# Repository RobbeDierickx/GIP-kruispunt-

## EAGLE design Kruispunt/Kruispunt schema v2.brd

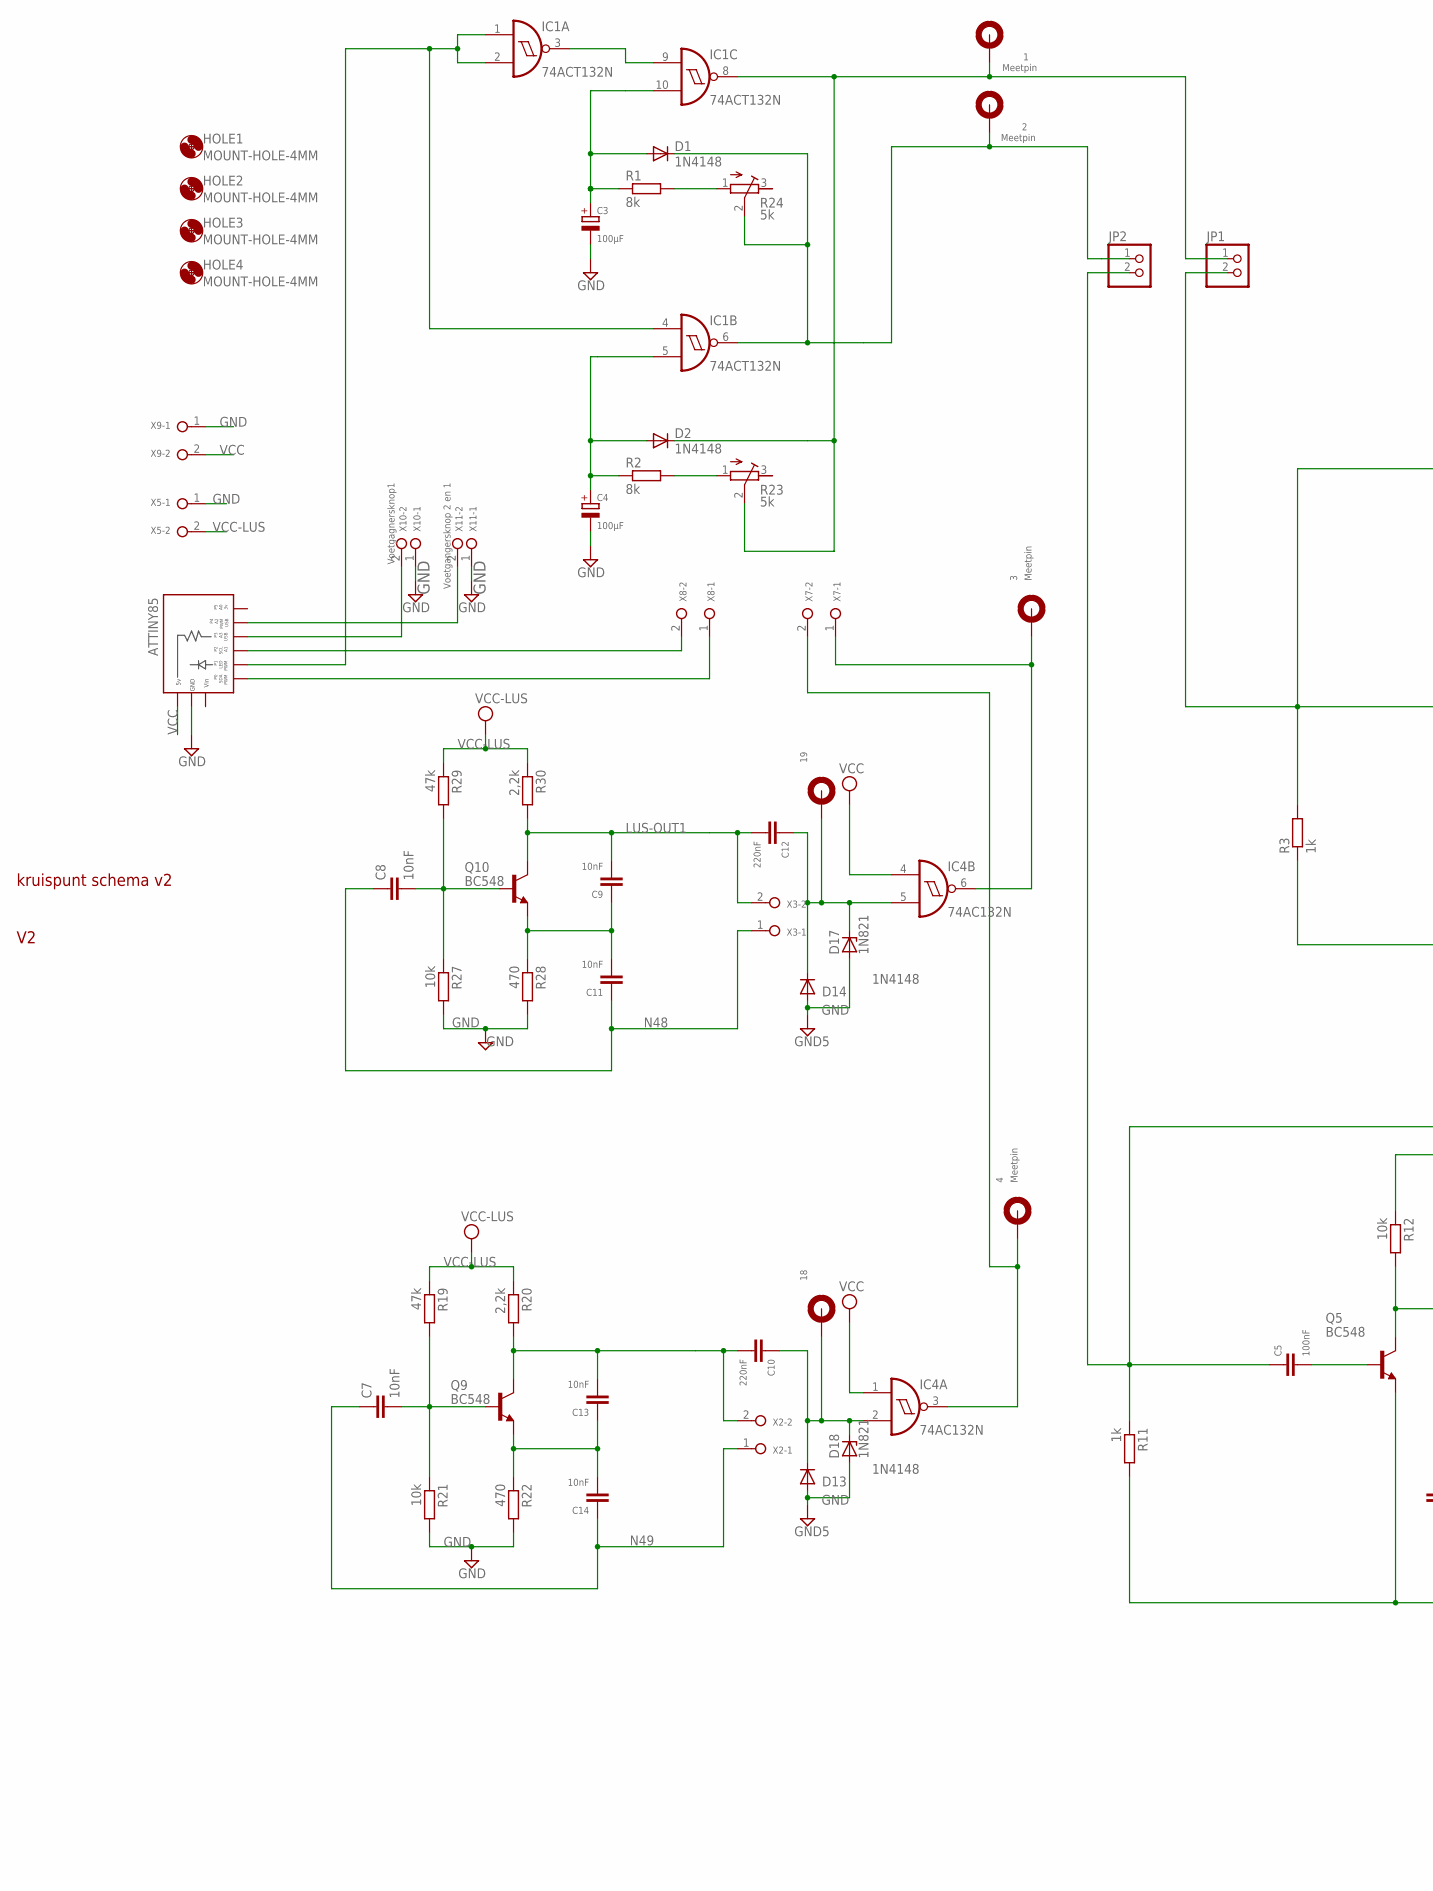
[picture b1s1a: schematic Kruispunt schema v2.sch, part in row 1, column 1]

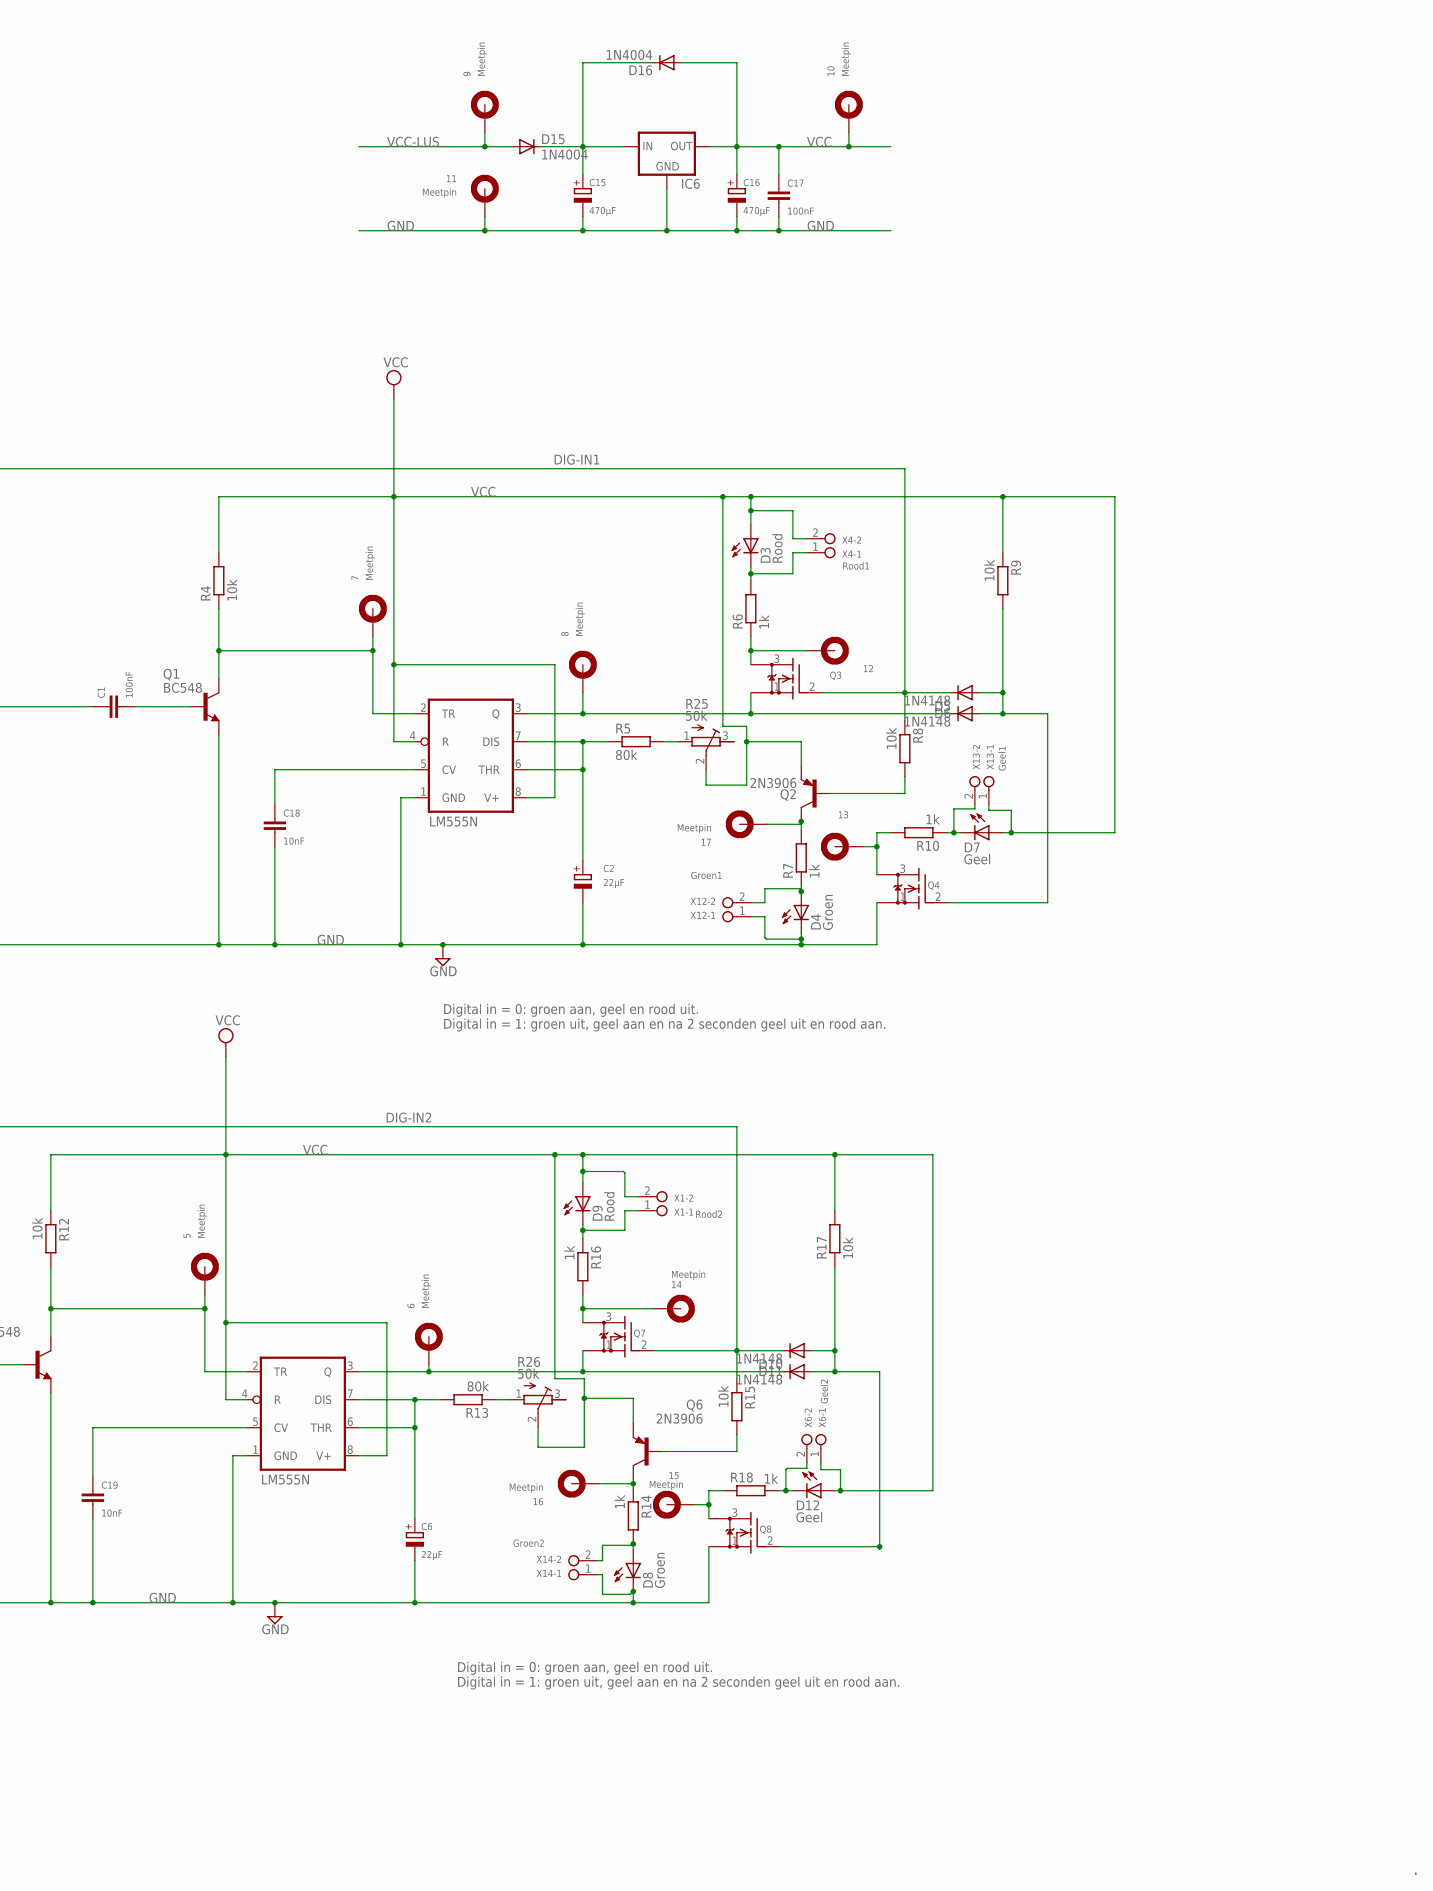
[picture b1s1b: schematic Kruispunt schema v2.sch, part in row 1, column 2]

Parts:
1, 2, 3, 4, 5, 6, 7, 8, 9, 10, 11, 14, 15, 16, 17: Meetpin; PAD
12, 13, 18, 19: WIREPAD; PAD
ATTINY85: DIGISPARK
C1, C5, C17: 100nF; CERAMIC-CAP-C050-025X075
C2, C6: 22µF; ELCO-2.5MMLEAD
C3, C4: 100µF; ELCO-2.5MMLEAD
C7, C8, C9, C11, C13, C14, C18, C19: 10nF; CERAMIC-CAP-C050-025X075
C10, C12: 220nF; CERAMIC-CAP-C025_050-035X075
C15, C16: 470µF; ELCO-5,0MMLEAD
D1, D2, D5, D6, D10, D11, D13, D14: 1N4148; DO35-7
D3, D9: Rood; LED3MM
D4, D8: Groen; LED3MM
D7, D12: Geel; LED3MM
D15, D16: 1N4004; DO35-7
D17, D18: 1N821; DO35Z10
HOLE1, HOLE2, HOLE3, HOLE4: MOUNT-HOLE-4MM; 4,0
IC1: 74ACT132N; DIL14
IC2, IC3: LM555N; DIL08
IC4: 74AC132N; DIL14
IC6: LM78XX-TO220LM78XX-HEATSINK; LM78XX-HEATSINK
JP1, JP2: PINHD-1X2; 1X02
Q1, Q5, Q9, Q10: BC548; TO92-CBE
Q2, Q6: 2N3906; TO92-EBC
Q3, Q4, Q7, Q8: 2N7000; TO-92
R1, R2: 8k; 0207/10
R3, R6, R7, R10, R11, R14, R16, R18: 1k; 0207/10
R4, R8, R9, R12, R15, R17, R21, R27: 10k; 0207/10
R5, R13: 80k; 0207/10
R19, R29: 47k; 0207/10
R20, R30: 2,2k; 0207/10
R22, R28: 470; 0207/10
R23, R24: 5k; RTRIM64W
R25, R26: 50k; RTRIM64W
X1: Rood2; W237-132
X2, X3, X5, X7, X8, X9: TERMINAL-5MM-2POLE; W237-132
X4: Rood1; W237-132
X6: Geel2; W237-132
X10: Voetgagnersknop1; W237-132
X11: Voetgangersknop 2 en 1; W237-132
X12: Groen1; W237-132
X13: Geel1; W237-132
X14: Groen2; W237-132

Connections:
DIG-IN1: C1.P$2, D6.C, JP1.2, Q3.2 (G), R3.2, R8.1
DIG-IN2: C5.P$2, D11.C, JP2.2, Q7.2 (G), R11.1, R15.1
GND: 11.P$1, ATTINY85.GND, ATTINY85.GND1 (GND), C2.-, C3.-, C4.-, C6.-, C15.-, C16.-, C17.P$1, C18.P$1, C19.P$1, D4.K (C), D8.K (C), D13.A, D14.A, D17.A, D18.A, IC1.7 (GND), IC2.1 (GND), IC3.1 (GND), IC4.7 (GND), IC6.GND, Q1.E, Q4.1 (S), Q5.E, Q8.1 (S), R3.1, R11.2, R21.2, R22.2, R27.2, R28.2, X5.1, X9.1, X10.1, X11.1, X12.1, X14.1
LUS-OUT1: C9.P$1, C12.P$1, Q10.C, R30.2, X3.2
N48: C8.P$2, C11.P$2, X3.1
N49: C7.P$2, C14.P$2, X2.1
unnamed: C4.+, D2.A, IC1.5 (I1), R2.1
unnamed: IC1.3 (O), IC1.9 (I0)
unnamed: ATTINY85.P1, IC1.1 (I0), IC1.2 (I1), IC1.4 (I0)
unnamed: C1.P$1, Q1.B
unnamed: R13.1, R26.1 (A)
unnamed: 1.P$1, D2.C, IC1.8 (O), JP1.1, R23.2 (S)
unnamed: C3.+, D1.A, IC1.10 (I1), R1.1
unnamed: 7.P$1, IC2.2 (TR), Q1.C, R4.1
unnamed: C2.+, IC2.6 (THR), IC2.7 (DIS), R5.1
unnamed: 17.P$1, Q2.C, R7.2
unnamed: D4.A, R7.1, X12.2
unnamed: Q2.B, R8.2
unnamed: 12.P$1, Q3.3 (D), R6.1
unnamed: D3.K (C), R6.2, X4.1
unnamed: 8.P$1, D5.C, IC2.3 (Q), Q3.1 (S)
unnamed: R2.2, R23.1 (A)
unnamed: 13.P$1, Q4.3 (D), R10.2
unnamed: D7.K (C), R10.1, X13.2
unnamed: C5.P$1, Q5.B
unnamed: 5.P$1, IC3.2 (TR), Q5.C, R12.2
unnamed: C6.+, IC3.6 (THR), IC3.7 (DIS), R13.2
unnamed: 16.P$1, Q6.C, R14.1
unnamed: D8.A, R14.2, X14.2
unnamed: Q6.B, R15.2
unnamed: 14.P$1, Q7.3 (D), R16.2
unnamed: ATTINY85.P3, X10.2
unnamed: 6.P$1, D10.C, IC3.3 (Q), Q7.1 (S)
unnamed: D10.A, D11.A, Q8.2 (G), R17.1
unnamed: 15.P$1, Q8.3 (D), R18.1
unnamed: D12.K (C), R18.2, X6.2
unnamed: C7.P$1, Q9.B, R19.2, R21.1
unnamed: C13.P$2, C14.P$1, Q9.E, R22.1
unnamed: C10.P$1, C13.P$1, Q9.C, R20.2, X2.2
unnamed: 18.P$1, C10.P$2, C10.P$3, D13.C, D18.C, IC4.2 (I1)
unnamed: 4.P$1, IC4.3 (O), X7.2
unnamed: R1.2, R24.1 (A)
unnamed: R5.2, R25.1 (A)
unnamed: C19.P$2, IC3.5 (CV)
unnamed: C8.P$1, Q10.B, R27.1, R29.2
unnamed: C9.P$2, C11.P$1, Q10.E, R28.1
unnamed: D5.A, D6.A, Q4.2 (G), R9.2
unnamed: 19.P$1, C12.P$2, C12.P$3, D14.C, D17.C, IC4.5 (I1)
unnamed: C18.P$2, IC2.5 (CV)
unnamed: 3.P$1, IC4.6 (O), X7.1
unnamed: C15.+, D15.C, D16.C, IC6.IN
unnamed: ATTINY85.P4, X11.2
unnamed: 2.P$1, D1.C, IC1.6 (O), JP2.1, R24.2 (S)
unnamed: ATTINY85.P2, X8.2
unnamed: D9.K (C), R16.1, X1.1
unnamed: ATTINY85.P0, X8.1
VCC: 10.P$1, ATTINY85.5V, ATTINY85.5V1 (5V), C16.+, C17.P$2, D3.A, D7.A, D9.A, D12.A, D16.A, IC1.14 (VCC), IC2.4 (R), IC2.8 (V+), IC3.4 (R), IC3.8 (V+), IC4.1 (I0), IC4.4 (I0), IC4.14 (VCC), IC6.OUT, Q2.E, Q6.E, R4.2, R9.1, R12.1, R17.2, R25.2 (S), R26.2 (S), X1.2, X4.2, X6.1, X9.2, X13.1
VCC-LUS: 9.P$1, D15.A, R19.1, R20.1, R29.1, R30.1, X5.2
VIN: ATTINY85.VIN, ATTINY85.VIN1 (VIN)

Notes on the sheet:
Digital in = 0: groen aan, geel en rood uit. Digital in = 1: groen uit, geel aan en na 2 seconden geel uit en rood aan.

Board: 2 copper layers, 122 parts (0 on the bottom side), 59 nets, no tracks yet.

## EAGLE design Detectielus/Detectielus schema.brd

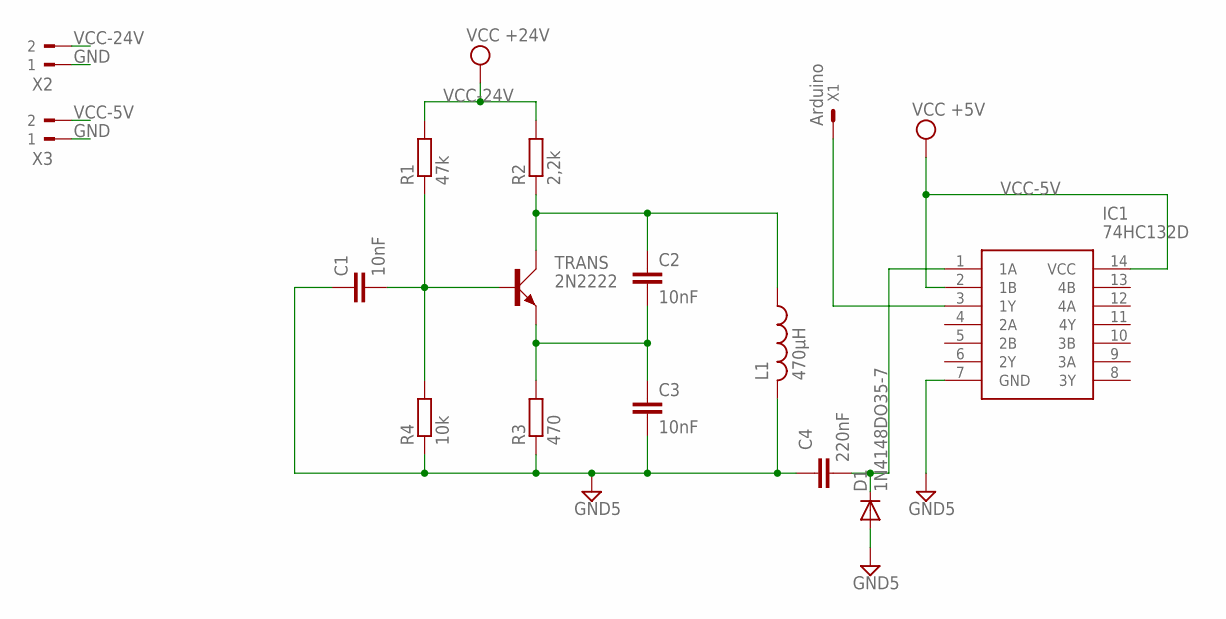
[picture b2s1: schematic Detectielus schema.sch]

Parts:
C1, C2, C3: 10nF; C050-024X044
C4: 220nF; C050-024X044
D1: 1N4148DO35-7; DO35-7
IC1: 74HC132D; SOIC127P600X175-14N
L1: 470µH; IR-4
R1: 47k; RDH/15
R2: 2,2k; RDH/15
R3: 470; RDH/15
R4: 10k; RDH/15
TRANS: 2N2222; TO220AV
X1: Arduino; 332-02
X2, X3: 90-2

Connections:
GND: X2.1, X3.1
GND5: C1.1, C3.2, C4.1, D1.A, IC1.7 (GND), L1.2, R3.1, R4.1
unnamed: C4.2, D1.C, IC1.1 (1A)
unnamed: C1.2, R1.1, R4.2, TRANS.B
unnamed: C2.2, C3.1, R3.2, TRANS.E
unnamed: C2.1, L1.1, R2.1, TRANS.C
unnamed: IC1.3 (1Y), X1.1
VCC-5V: IC1.2 (1B), IC1.14 (VCC), X3.2
VCC-24V: R1.2, R2.2, X2.2

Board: 2 copper layers, 15 parts (0 on the bottom side), 9 nets, no tracks yet.

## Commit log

2018-11-06 Scuft toegevoegd
2018-11-06 Bestanden opgeschoond
2018-11-06 gipblad
2018-11-09 update gip
2018-11-09 Gip update
2018-11-12 Detectielus Eagle schema
2018-11-13 Administratie
2018-11-15 Aanpassing schema (diode)
2018-11-15 Schema's en logboek
2018-11-16 Schema lichtsturing + logboek
2018-11-18 Logboek
2018-11-20 Vertragingsschema
2018-11-20 Schema vertraging aanpassing
2018-11-22 hardwaresturing aanpassing + logboek
2018-11-23 Schema lichten aanpassing + logboek
2018-11-26 Schema lichtsturing, library eindbord, Logboek
2018-11-27 Kruispunt
2018-11-27 Kruispunt schema + logboek + lichten programma
2018-11-29 eindschema + logboek
2018-11-30 Bord kruispunt + library aanpassing + logboek
2018-12-03 Bord en schema + logboek
2018-12-04 Schema + logboek
2018-12-04 logboek en schema
2019-01-05 schema
2019-01-10 Schema en ppt
2019-01-11 Schema, gerber, logboek
2019-01-14 frequentieteller + logboek
2019-01-15 Logboek+ programma
2019-01-18 kruipunt logboek
2019-01-25 Logboek programme isp
2019-02-03 log
    log
2019-02-07 log +kruispitb
2019-02-12 schema v2
2019-02-26 fsre
2019-02-28 logboek en kruispunt
2019-04-02 epic
2019-04-23 v3 gerber verslag
2019-04-26 logboek en gip map
2019-04-26 yeet
2019-05-07 rzgzrg
2019-05-22 reeed
2019-05-24 documztn
2019-05-24 mpkj
2019-05-27 Doxs
2019-05-28 reee
